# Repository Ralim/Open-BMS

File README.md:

# Open-BMS
ISL94202 &amp; MSP430 based BMS

This is the source files for the Open BMS Designed by Ben V. Brown.
Documentation is currently over at [Hackaday.io](https://hackaday.io/project/25512-open-bms).

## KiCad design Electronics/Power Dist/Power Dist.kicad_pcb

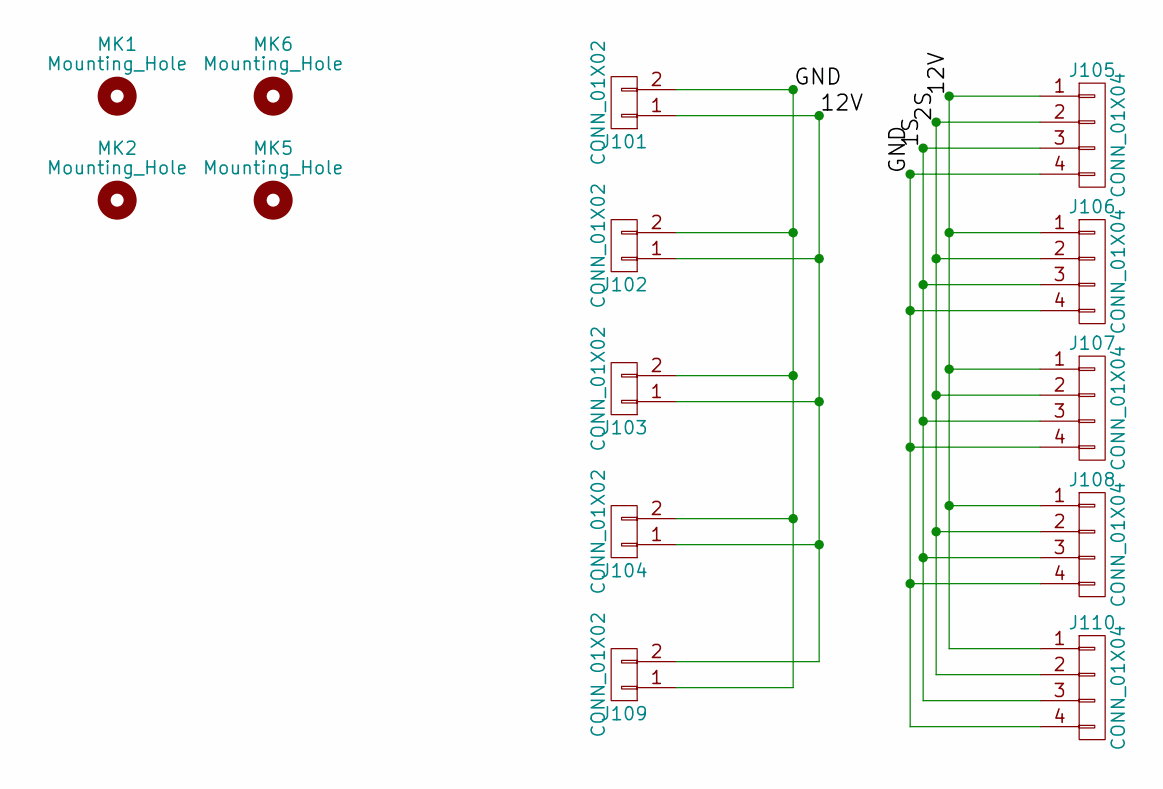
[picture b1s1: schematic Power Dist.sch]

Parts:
J101: CONN_01X02; XT30PW_Female
J102, J103, J104: CONN_01X02; XT30PW_Male
J105, J106, J107, J108: CONN_01X04; JST_XH_S04B-XH-A_04x2.50mm_Angled
J109: CONN_01X02; XT30
J110: CONN_01X04; JST_XH_B04B-XH-A_04x2.50mm_Straight
MK1, MK2, MK5, MK6: Mounting_Hole; MountingHole_3.2mm_M3

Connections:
/1S: J105.3, J106.3, J107.3, J108.3, J110.3
/2S: J105.2, J106.2, J107.2, J108.2, J110.2
/12V: J101.1, J102.1, J103.1, J104.1, J105.1, J106.1, J107.1, J108.1, J109.2, J110.1
/GND: J101.2, J102.2, J103.2, J104.2, J105.4, J106.4, J107.4, J108.4, J109.1, J110.4

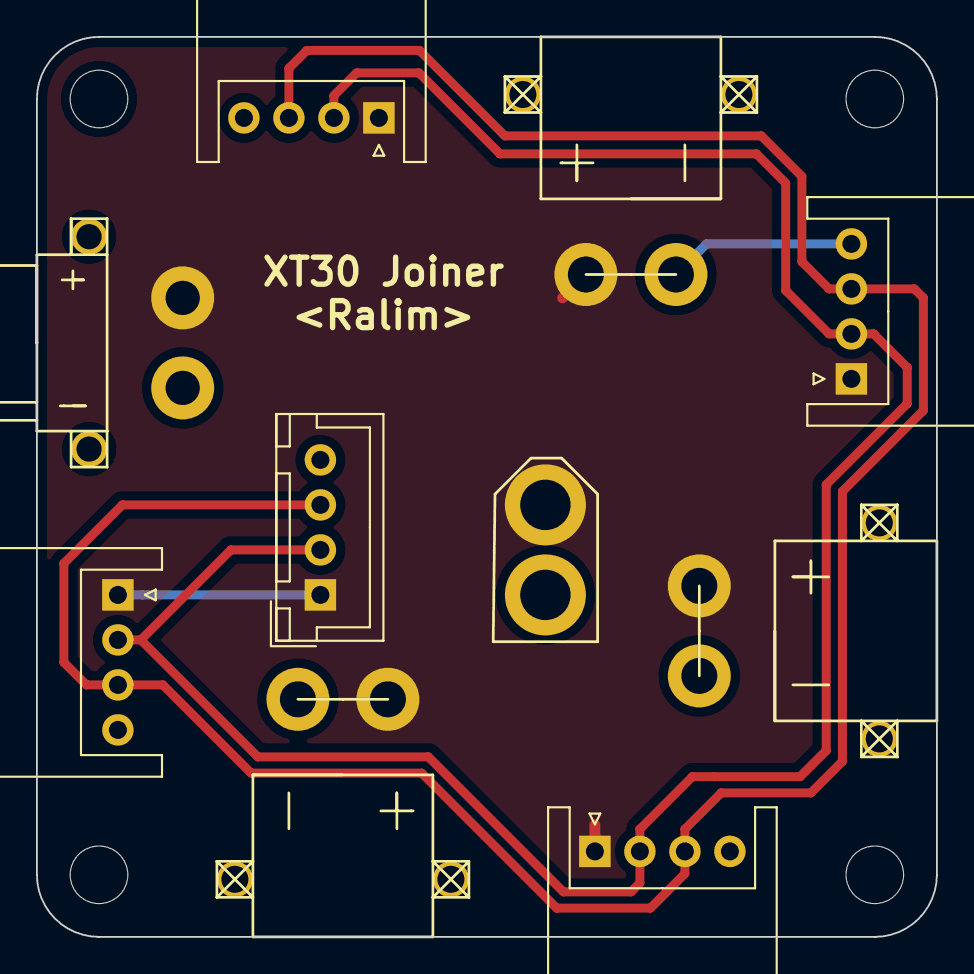
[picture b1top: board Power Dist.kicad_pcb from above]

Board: 2 copper layers, 50.0 x 50.0 mm, 14 parts (0 on the bottom side), 4 nets.

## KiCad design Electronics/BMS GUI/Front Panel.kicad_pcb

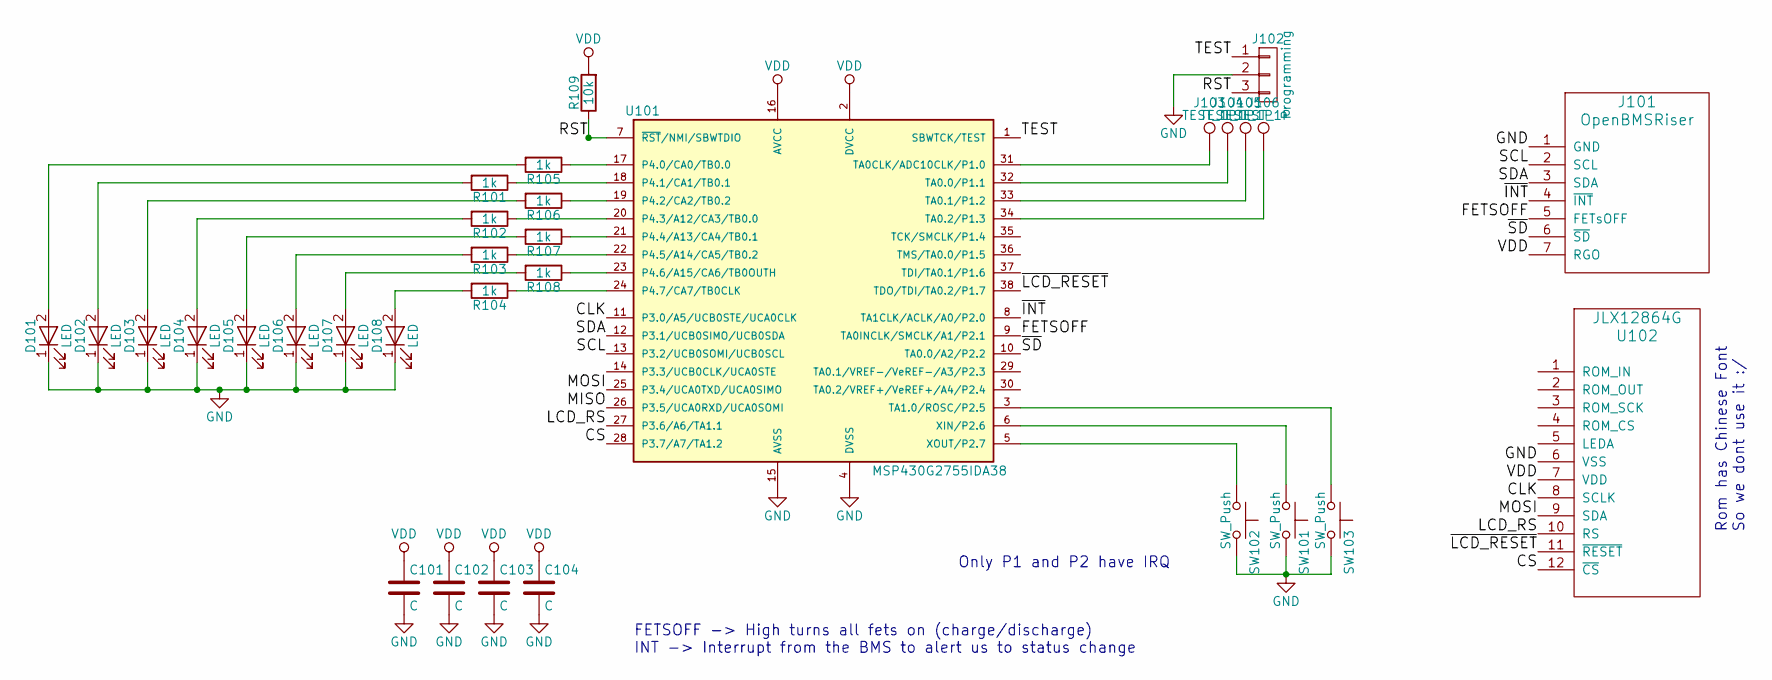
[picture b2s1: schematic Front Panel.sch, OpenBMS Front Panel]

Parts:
C101, C102, C103, C104: C; C_0603
D101, D102, D103, D104, D105, D106, D107, D108: LED; LED_0805
J101: OpenBMSRiser
J102: Programming; Pin_Header_Angled_1x03_Pitch2.54mm
J103, J104, J105, J106: TEST_1P; TEST-SMD-SMALL
R101, R102, R103, R104, R105, R106, R107, R108: 1k; R_0603
R109: 10k; R_0603
SW101, SW102, SW103: SW_Push; SW_SPST_TL3342
U101: MSP430G2755IDA38; TSSOP-38_4.4x9.7mm_Pitch0.5mm
U102: JLX12864G

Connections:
/CLK: U101.11 (P3.0/A5/UCB0STE/UCA0CLK), U102.8 (SCLK)
/CS: U101.28 (P3.7/A7/TA1.2), U102.12 (~CS)
/FETSOFF: J101.5 (FETsOFF), U101.9 (TA0INCLK/SMCLK/A1/P2.1)
/LCD_RS: U101.27 (P3.6/A6/TA1.1), U102.10 (RS)
/MOSI: U101.25 (P3.4/UCA0TXD/UCA0SIMO), U102.9 (SDA)
/RST: J102.3, R109.1, U101.7 (~RST~/NMI/SBWTDIO)
/SCL: J101.2 (SCL), U101.13 (P3.2/UCB0SOMI/UCB0SCL)
/SDA: J101.3 (SDA), U101.12 (P3.1/UCB0SIMO/UCB0SDA)
/TEST: J102.1, U101.1 (SBWTCK/TEST)
/~INT: J101.4 (~INT), U101.8 (TA1CLK/ACLK/A0/P2.0)
/~LCD_RESET: U101.38 (TDO/TDI/TA0.2/P1.7), U102.11 (~RESET)
/~SD: J101.6 (~SD), U101.10 (TA0.0/A2/P2.2)
GND: C101.2, C102.2, C103.2, C104.2, D101.1 (K), D102.1 (K), D103.1 (K), D104.1 (K), D105.1 (K), D106.1 (K), D107.1 (K), D108.1 (K), J101.1 (GND), J102.2, SW101.2, SW102.2, SW103.2, U101.4 (DVSS), U101.15 (AVSS), U102.6 (VSS)
unnamed: D101.2 (A), R105.2
unnamed: D102.2 (A), R101.2
unnamed: D103.2 (A), R106.2
unnamed: D104.2 (A), R102.2
unnamed: D105.2 (A), R107.2
unnamed: D106.2 (A), R103.2
unnamed: D107.2 (A), R108.2
unnamed: D108.2 (A), R104.2
unnamed: J103.1, U101.31 (TA0CLK/ADC10CLK/P1.0)
unnamed: J104.1, U101.32 (TA0.0/P1.1)
unnamed: J105.1, U101.33 (TA0.1/P1.2)
unnamed: J106.1, U101.34 (TA0.2/P1.3)
unnamed: R101.1, U101.18 (P4.1/CA1/TB0.1)
unnamed: R102.1, U101.20 (P4.3/A12/CA3/TB0.0)
unnamed: R103.1, U101.22 (P4.5/A14/CA5/TB0.2)
unnamed: R104.1, U101.24 (P4.7/CA7/TB0CLK)
unnamed: R105.1, U101.17 (P4.0/CA0/TB0.0)
unnamed: R106.1, U101.19 (P4.2/CA2/TB0.2)
unnamed: R107.1, U101.21 (P4.4/A13/CA4/TB0.1)
unnamed: R108.1, U101.23 (P4.6/A15/CA6/TB0OUTH)
unnamed: SW101.1, U101.6 (XIN/P2.6)
unnamed: SW102.1, U101.5 (XOUT/P2.7)
unnamed: SW103.1, U101.3 (TA1.0/ROSC/P2.5)
VDD: C101.1, C102.1, C103.1, C104.1, J101.7 (RGO), R109.2, U101.2 (DVCC), U101.16 (AVCC), U102.7 (VDD)

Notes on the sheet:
Rom has Chinese Font So we dont use it :/
Only P1 and P2 have IRQ
FETSOFF -> High turns all fets on (charge/discharge) INT -> Interrupt from the BMS to alert us to status change

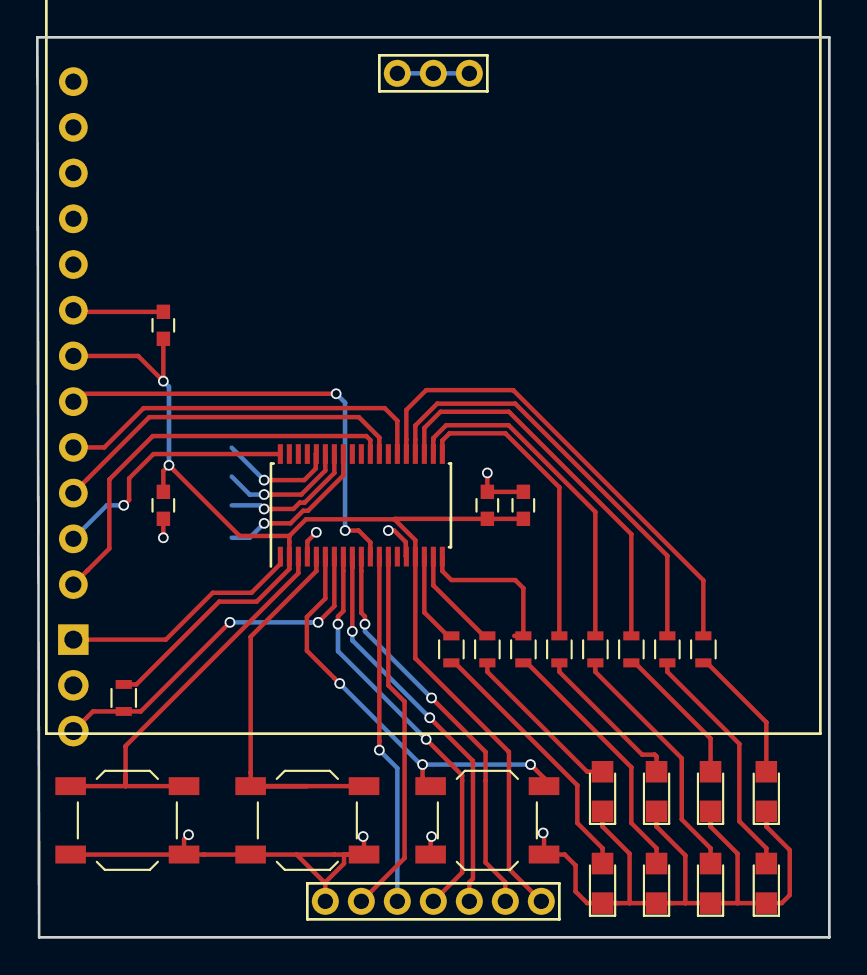
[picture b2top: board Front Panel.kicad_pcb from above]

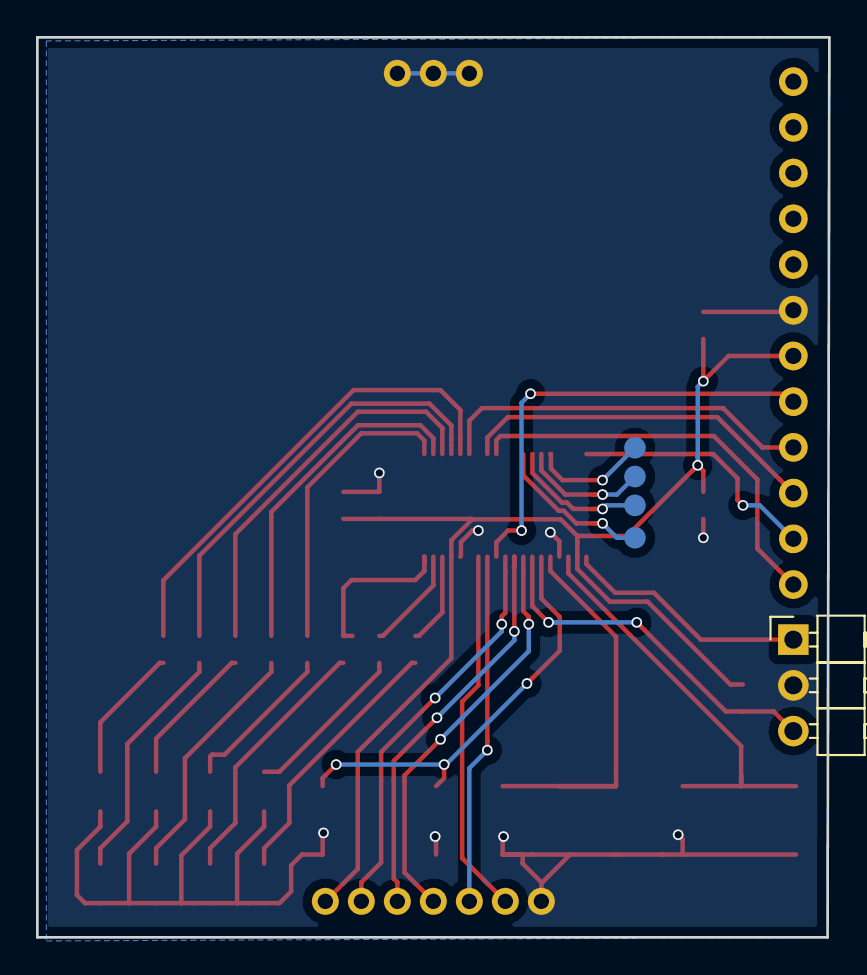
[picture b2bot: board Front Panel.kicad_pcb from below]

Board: 2 copper layers, 44.0 x 50.0 mm, 32 parts (5 on the bottom side), 37 nets.

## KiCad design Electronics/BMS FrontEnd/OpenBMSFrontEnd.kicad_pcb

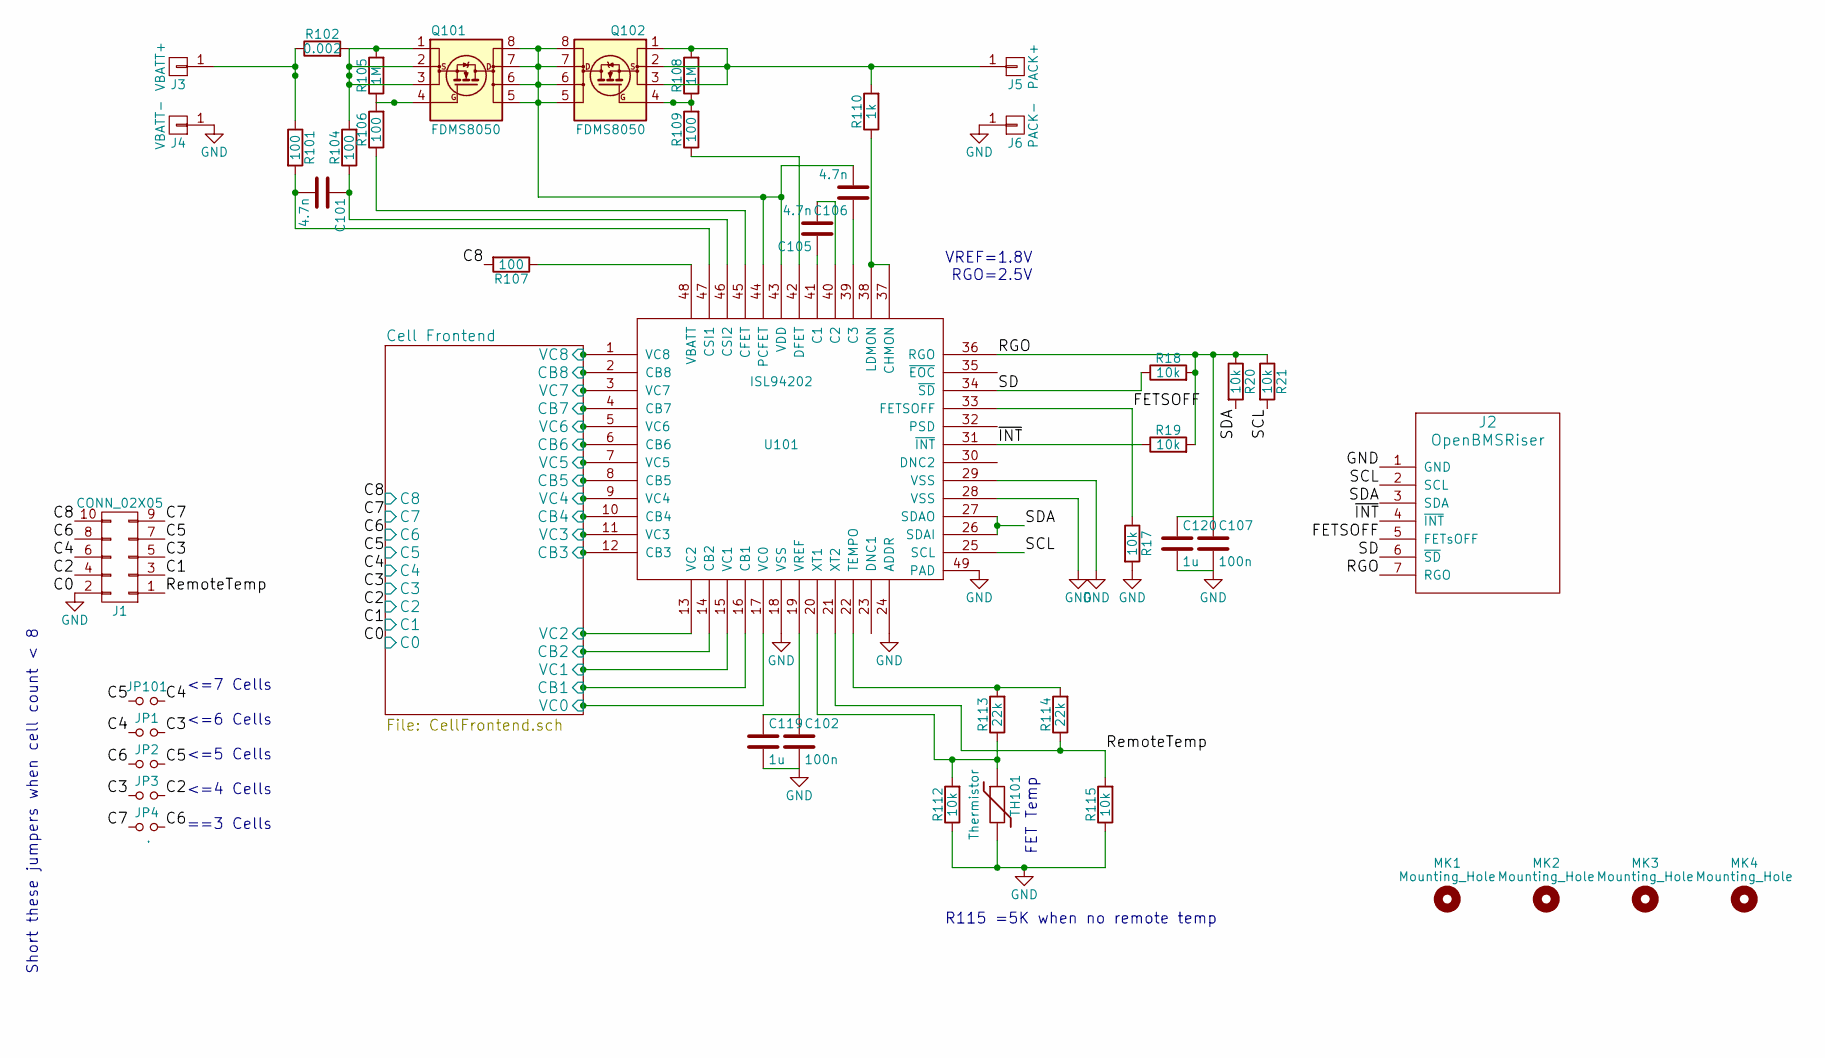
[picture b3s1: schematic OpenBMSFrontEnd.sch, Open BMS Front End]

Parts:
C101, C105, C106: 4.7n; C_0603
C102, C107: 100n; C_0603
C119, C120: 1u; C_0603
J1: CONN_02X05; IDC_Header_Straight_10pins
J2: OpenBMSRiser
J3: VBATT+; SolderWirePad_single_2mmDrill
J4: VBATT-; SolderWirePad_single_2mmDrill
J5: PACK+; SolderWirePad_single_2mmDrill
J6: PACK-; SolderWirePad_single_2mmDrill
JP1, JP2, JP3, JP4, JP101: .; JUMPER-SOLDER-SMD
MK1, MK2, MK3, MK4: Mounting_Hole; MountingHole_3.2mm_M3
Q101, Q102: FDMS8050; TDSON-8-1
R17, R18, R19, R20, R21, R112, R115: 10k; R_0603
R101, R104, R106, R107, R109: 100; R_0603
R102: 0.002; R_2512
R105, R108: 1M; R_0603
R110: 1k; R_0603
R113, R114: 22k; R_0603
TH101: Thermistor; R_0603
U101: ISL94202; UQFN-48-1EP_6x6mm_Pitch0.4mm

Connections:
/C1: J1.3; also elsewhere on the board
/C2: J1.4, JP3.2; also elsewhere on the board
/C3: J1.5, JP1.2, JP3.1; also elsewhere on the board
/C4: J1.6, JP1.1, JP101.2; also elsewhere on the board
/C5: J1.7, JP2.2, JP101.1; also elsewhere on the board
/C6: J1.8, JP2.1, JP4.2; also elsewhere on the board
/C7: J1.9, JP4.1; also elsewhere on the board
/C8: J1.10, R107.2; also elsewhere on the board
/Cell Frontend/CB1: U101.16 (CB1); also elsewhere on the board
/Cell Frontend/CB2: U101.14 (CB2); also elsewhere on the board
/Cell Frontend/CB3: U101.12 (CB3); also elsewhere on the board
/Cell Frontend/CB4: U101.10 (CB4); also elsewhere on the board
/Cell Frontend/CB5: U101.8 (CB5); also elsewhere on the board
/Cell Frontend/CB6: U101.6 (CB6); also elsewhere on the board
/Cell Frontend/CB7: U101.4 (CB7); also elsewhere on the board
/Cell Frontend/CB8: U101.2 (CB8); also elsewhere on the board
/Cell Frontend/VC0: U101.17 (VC0); also elsewhere on the board
/Cell Frontend/VC1: U101.15 (VC1); also elsewhere on the board
/Cell Frontend/VC2: U101.13 (VC2); also elsewhere on the board
/Cell Frontend/VC3: U101.11 (VC3); also elsewhere on the board
/Cell Frontend/VC4: U101.9 (VC4); also elsewhere on the board
/Cell Frontend/VC5: U101.7 (VC5); also elsewhere on the board
/Cell Frontend/VC6: U101.5 (VC6); also elsewhere on the board
/Cell Frontend/VC7: U101.3 (VC7); also elsewhere on the board
/Cell Frontend/VC8: U101.1 (VC8); also elsewhere on the board
/FETSOFF: J2.5 (FETsOFF), R17.1, U101.33 (FETSOFF)
/RGO: C107.1, C120.1, J2.7 (RGO), R18.2, R19.2, R20.1, R21.1, U101.36 (RGO)
/RemoteTemp: J1.1, R114.1, R115.2, U101.21 (XT2)
/SCL: J2.2 (SCL), R21.2, U101.25 (SCL)
/SD: J2.6 (~SD), R18.1, U101.34 (~SD)
/SDA: J2.3 (SDA), R20.2, U101.26 (SDAI), U101.27 (SDAO)
/~INT: J2.4 (~INT), R19.1, U101.31 (~INT)
GND: C102.2, C107.2, C119.2, C120.2, J1.2, J2.1 (GND), J4.1, J6.1, R17.2, R112.1, R115.1, TH101.2, U101.18 (VSS), U101.24 (ADDR), U101.28 (VSS), U101.29 (VSS), U101.49 (PAD); also elsewhere on the board
unnamed: C101.1, R104.1, U101.46 (CSI2)
unnamed: C101.2, R101.2, U101.47 (CSI1)
unnamed: C102.1, C119.1, U101.19 (VREF)
unnamed: C105.1, U101.41 (C1)
unnamed: C105.2, U101.40 (C2)
unnamed: C106.1, U101.39 (C3)
unnamed: C106.2, Q101.5 (D), Q101.6 (D), Q101.7 (D), Q101.8 (D), Q102.5 (D), Q102.6 (D), Q102.7 (D), Q102.8 (D), U101.43 (VDD), U101.44 (PCFET)
unnamed: J3.1, R101.1, R102.1
unnamed: J5.1, Q102.1 (S), Q102.2 (S), Q102.3 (S), R108.2, R110.2
unnamed: Q101.1 (S), Q101.2 (S), Q101.3 (S), R102.2, R104.2, R105.2
unnamed: Q101.4 (G), R105.1, R106.2
unnamed: Q102.4 (G), R108.1, R109.2
unnamed: R106.1, U101.45 (CFET)
unnamed: R107.1, U101.48 (VBATT)
unnamed: R109.1, U101.42 (DFET)
unnamed: R110.1, U101.37 (CHMON), U101.38 (LDMON)
unnamed: R112.2, R113.1, TH101.1, U101.20 (XT1)
unnamed: R113.2, R114.2, U101.22 (TEMPO)

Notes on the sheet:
VREF=1.8V RGO=2.5V
FET Temp
<=7 Cells <=6 Cells <=5 Cells <=4 Cells ==3 Cells
Short these jumpers when cell count < 8
R115 =5K when no remote temp

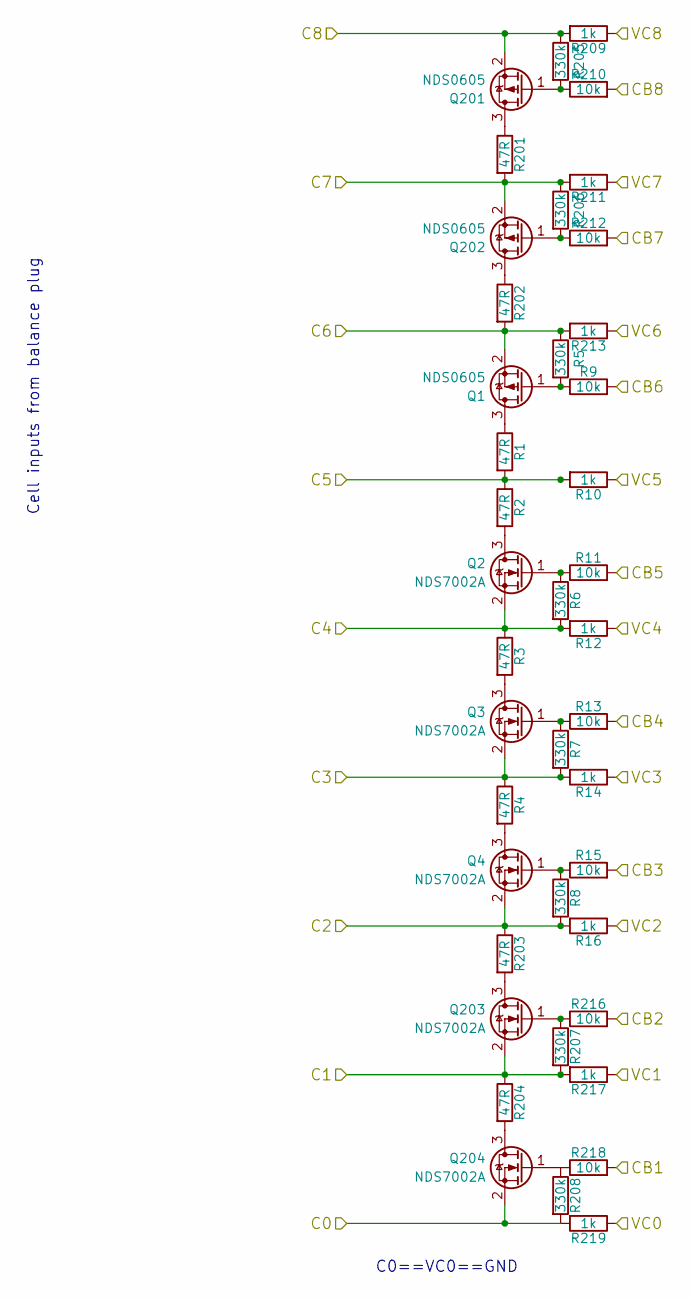
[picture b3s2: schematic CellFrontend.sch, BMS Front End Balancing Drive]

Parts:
Q1, Q201, Q202: NDS0605; SOT-23
Q2, Q3, Q4, Q203, Q204: NDS7002A; SOT-23
R1, R2, R3, R4, R201, R202, R203, R204: 47R; R_0805
R5, R6, R7, R8, R205, R206, R207, R208: 330k; R_0603
R9, R11, R13, R15, R210, R212, R216, R218: 10k; R_0603
R10, R12, R14, R16, R209, R211, R213, R217, R219: 1k; R_0603

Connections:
/C1: Q203.2 (S), R204.1, R207.2, R217.2; also elsewhere on the board
/C2: Q4.2 (S), R8.2, R16.2, R203.1; also elsewhere on the board
/C3: Q3.2 (S), R4.1, R7.2, R14.2; also elsewhere on the board
/C4: Q2.2 (S), R3.1, R6.2, R12.2; also elsewhere on the board
/C5: R1.2, R2.1, R10.2; also elsewhere on the board
/C6: Q1.2 (S), R5.1, R202.2, R213.2; also elsewhere on the board
/C7: Q202.2 (S), R201.2, R206.1, R211.2; also elsewhere on the board
/C8: Q201.2 (S), R205.1, R209.2; also elsewhere on the board
/Cell Frontend/CB1: R218.2; also elsewhere on the board
/Cell Frontend/CB2: R216.2; also elsewhere on the board
/Cell Frontend/CB3: R15.2; also elsewhere on the board
/Cell Frontend/CB4: R13.2; also elsewhere on the board
/Cell Frontend/CB5: R11.2; also elsewhere on the board
/Cell Frontend/CB6: R9.2; also elsewhere on the board
/Cell Frontend/CB7: R212.2; also elsewhere on the board
/Cell Frontend/CB8: R210.2; also elsewhere on the board
/Cell Frontend/VC0: R219.1; also elsewhere on the board
/Cell Frontend/VC1: R217.1; also elsewhere on the board
/Cell Frontend/VC2: R16.1; also elsewhere on the board
/Cell Frontend/VC3: R14.1; also elsewhere on the board
/Cell Frontend/VC4: R12.1; also elsewhere on the board
/Cell Frontend/VC5: R10.1; also elsewhere on the board
/Cell Frontend/VC6: R213.1; also elsewhere on the board
/Cell Frontend/VC7: R211.1; also elsewhere on the board
/Cell Frontend/VC8: R209.1; also elsewhere on the board
GND: Q204.2 (S), R208.2, R219.2; also elsewhere on the board
unnamed: Q1.1 (G), R5.2, R9.1
unnamed: Q1.3 (D), R1.1
unnamed: Q2.1 (G), R6.1, R11.1
unnamed: Q2.3 (D), R2.2
unnamed: Q3.1 (G), R7.1, R13.1
unnamed: Q3.3 (D), R3.2
unnamed: Q4.1 (G), R8.1, R15.1
unnamed: Q4.3 (D), R4.2
unnamed: Q201.1 (G), R205.2, R210.1
unnamed: Q201.3 (D), R201.1
unnamed: Q202.1 (G), R206.2, R212.1
unnamed: Q202.3 (D), R202.1
unnamed: Q203.1 (G), R207.1, R216.1
unnamed: Q203.3 (D), R203.2
unnamed: Q204.1 (G), R208.1, R218.1
unnamed: Q204.3 (D), R204.2

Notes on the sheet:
Cell inputs from balance plug
C0==VC0==GND

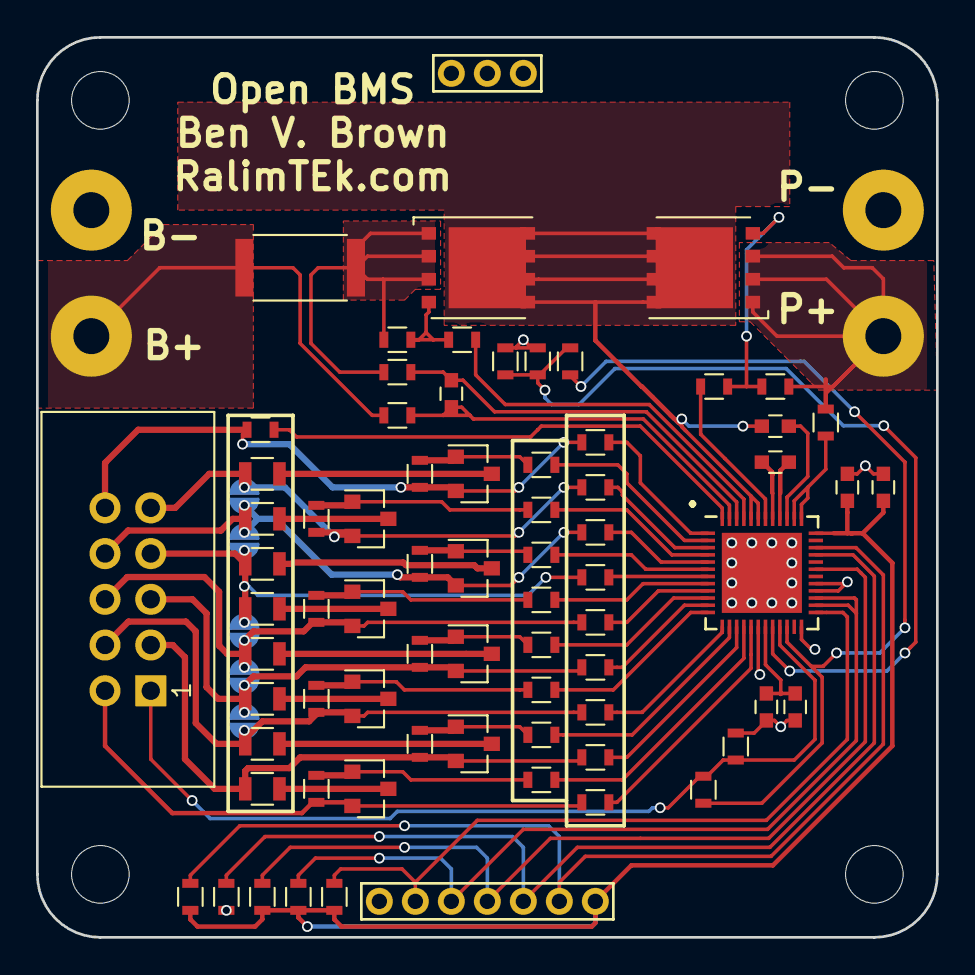
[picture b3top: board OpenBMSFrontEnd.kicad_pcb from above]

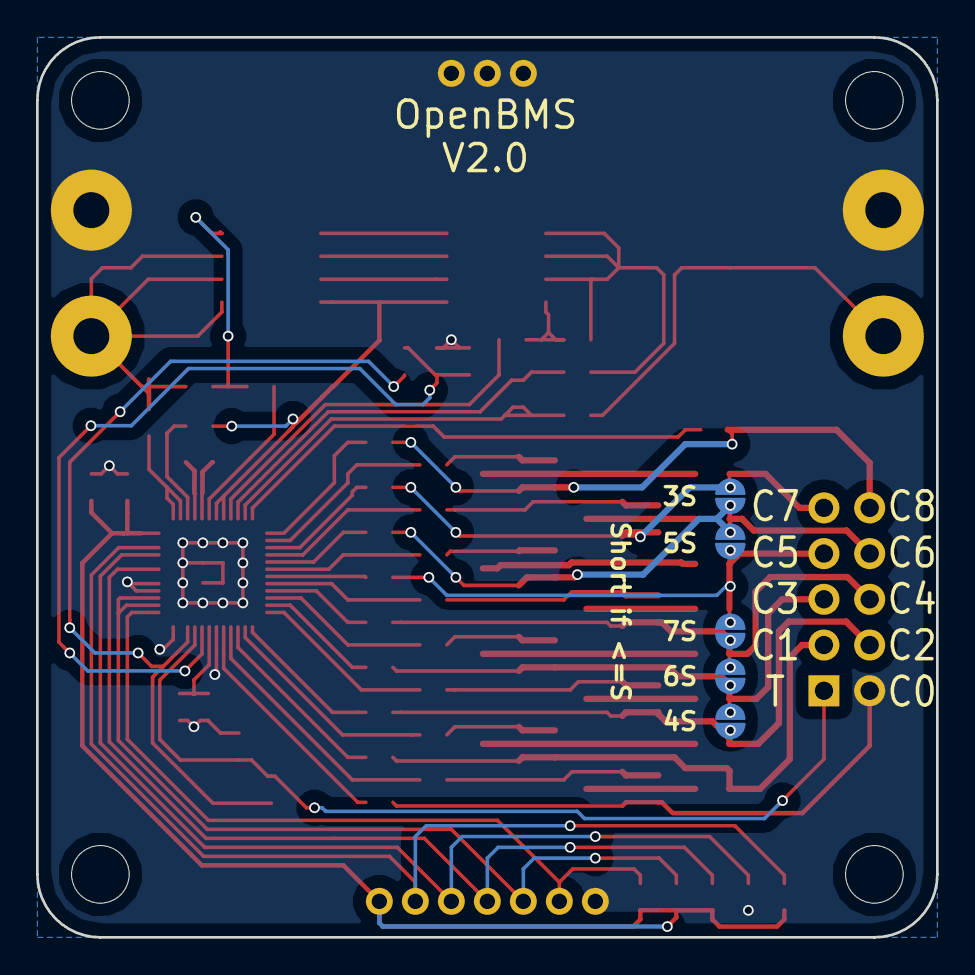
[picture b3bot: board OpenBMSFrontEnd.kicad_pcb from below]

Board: 2 copper layers, 50.0 x 50.0 mm, 85 parts (5 on the bottom side), 67 nets.

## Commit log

2017-06-18 Check In Baseboard & tester code
    + KiCad Design for base of the unit
    +Inital ISL code for I2C on the MSP430
2017-06-20 User Interface board layout rough pass
2017-07-08 Finish layout of front panel
2017-07-25 Add test code
2017-08-22 Add Power Dist PCB
2017-08-26 LCD printing working now
2017-08-27 Timer working
2017-08-29 Starting drawing the battery voltages for testing
2018-03-09 Changing absolute paths to relatives
2020-07-11 Create LICENSE.md
    Fixes Issue #2. Adds a license, based on MIT, but simplified to remove claim of, or requirements for, copyright.
